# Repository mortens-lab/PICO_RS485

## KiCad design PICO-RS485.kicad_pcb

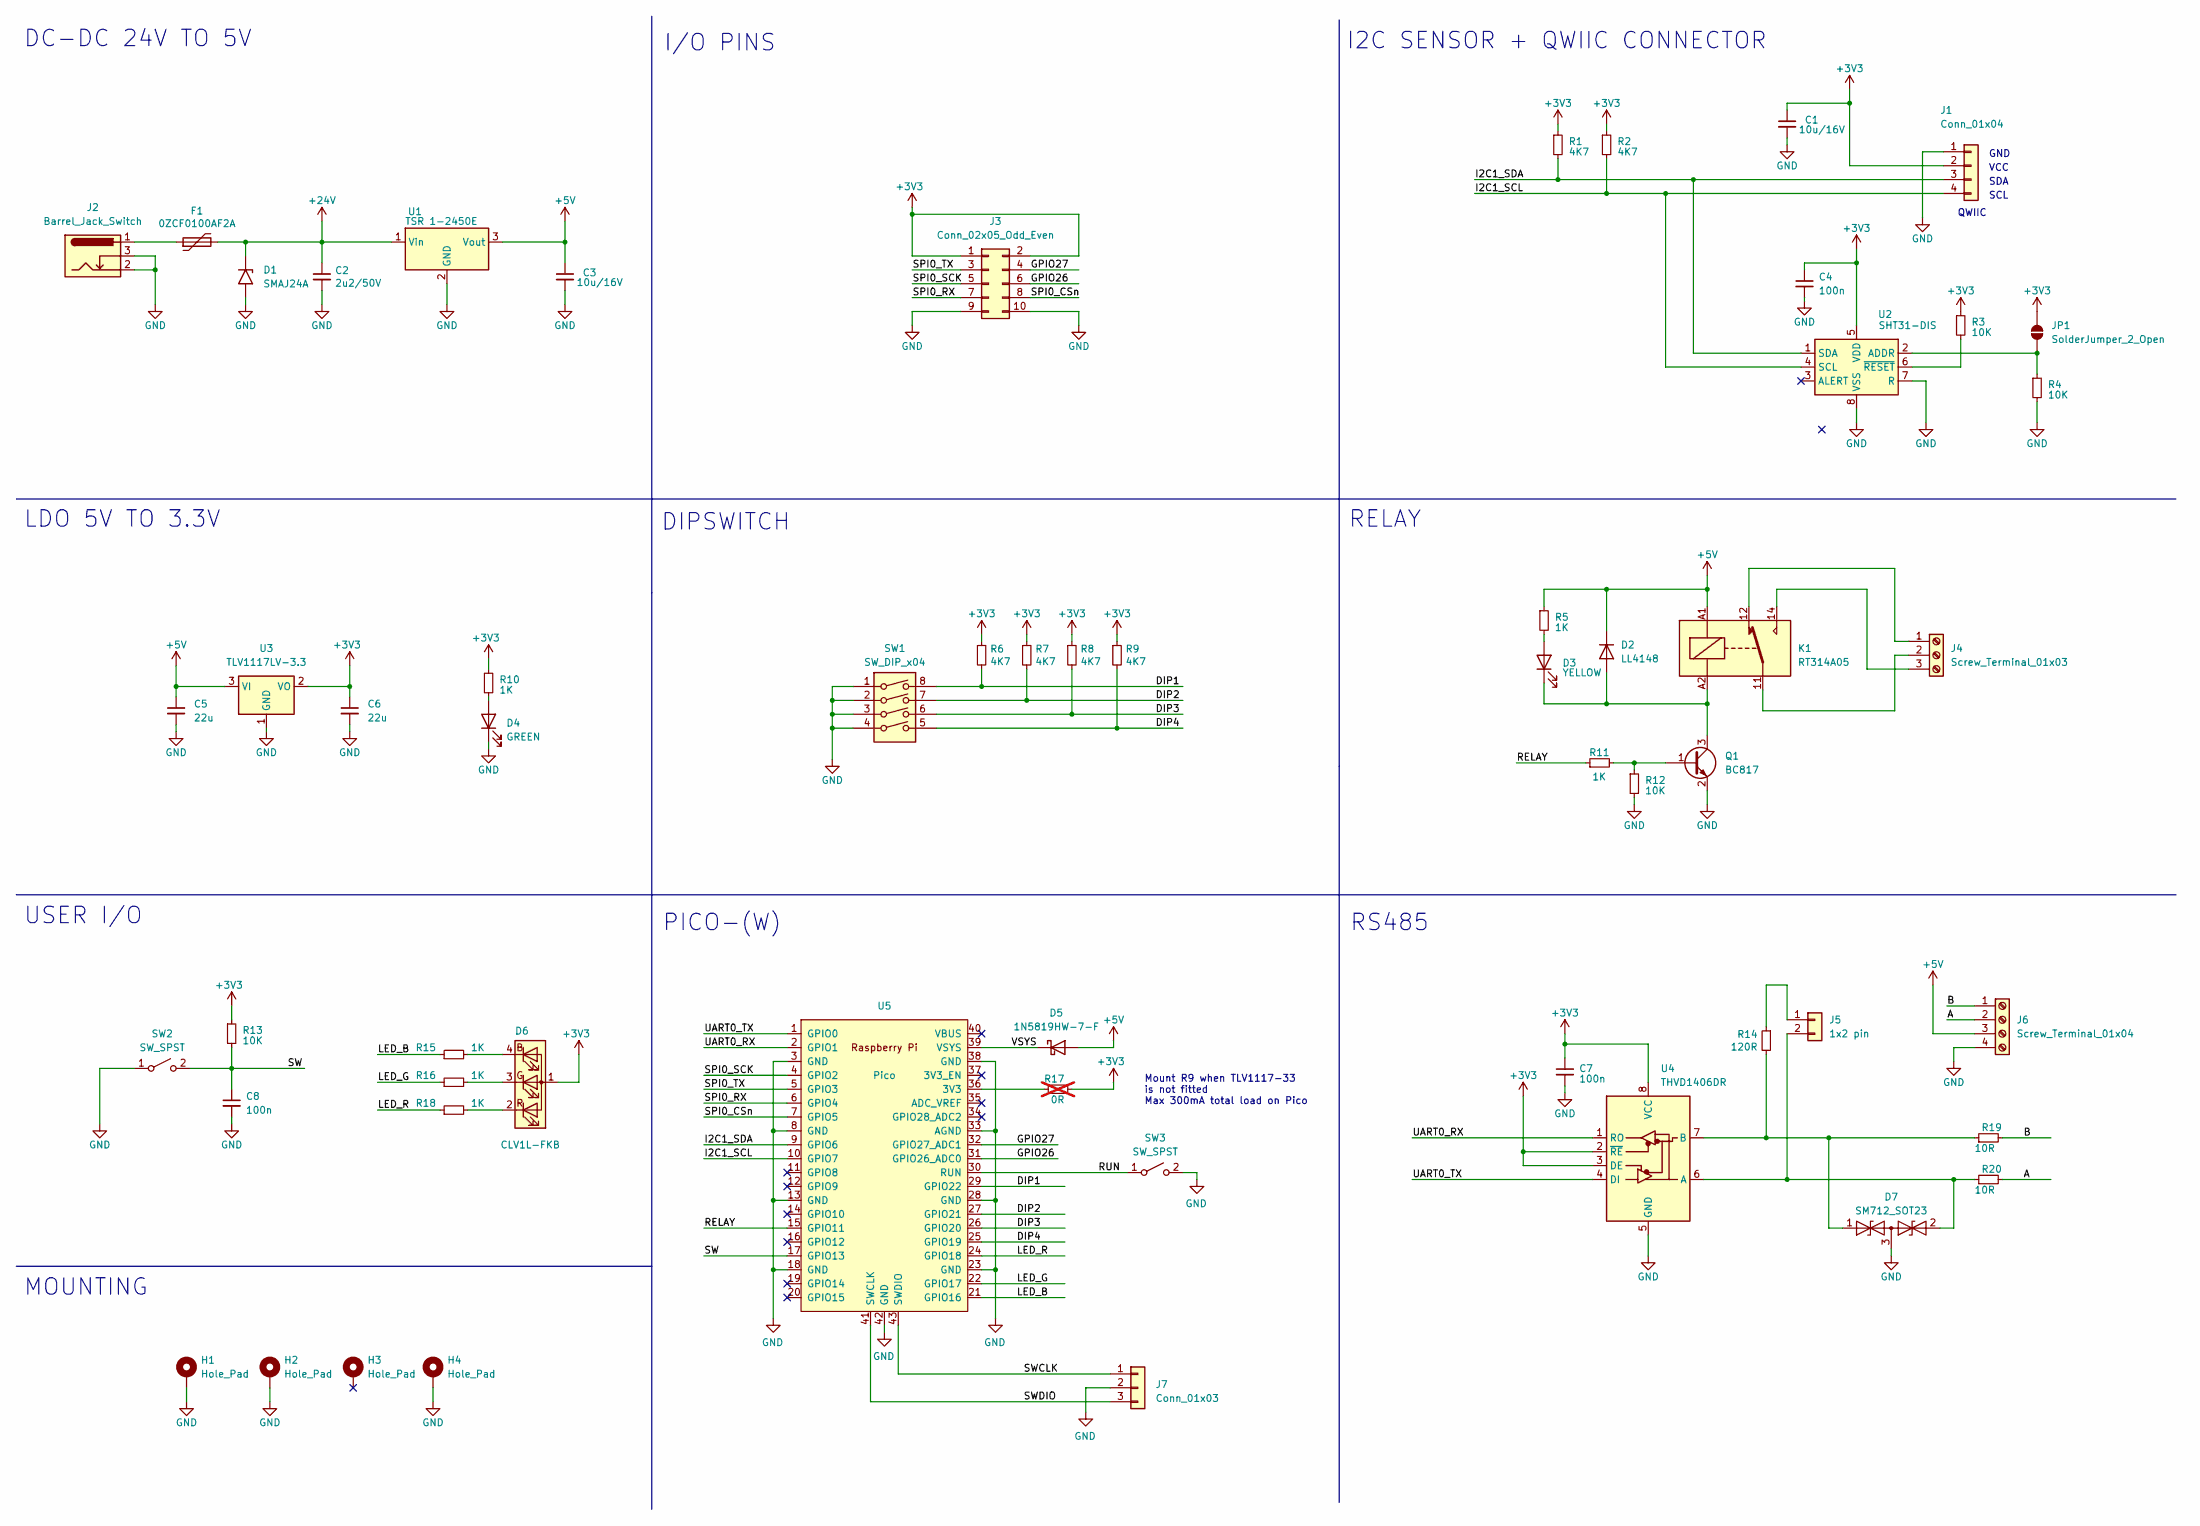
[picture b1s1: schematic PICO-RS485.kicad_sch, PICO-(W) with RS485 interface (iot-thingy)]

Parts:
C1, C3: 10u/16V; C_0805_2012Metric; Part Number CL21B106KOQNNNE; Mouser 187-CL21B106KOQNNNE
C2: 2u2/50V; C_0805_2012Metric; Part Number CL21B225KBYNNWE; Mouser 187-CL21B225KBYNNWE
C4, C7, C8: 100n; C_0402_1005Metric_Pad0.74x0.62mm_HandSolder; Manufacturer Part # GCM155R71H104KE02J; LCSC C2649549
C5, C6: 22u; C_0805_2012Metric_Pad1.18x1.45mm_HandSolder; Manufacturer Part # GRM21BR61A226ME51L; LCSC C77074
D1: SMAJ24A; D_SMA; Manufacturer Part # SMAJ24A; LCSC C148222
D2: LL4148; D_MiniMELF; Manufacturer Part # LL4148; LCSC C402260
D3: YELLOW; LED_0603_1608Metric_Pad1.05x0.95mm_HandSolder; Manufacturer Part # APTD1608LSYCK; LCSC C5352634
D4: GREEN; LED_0603_1608Metric_Pad1.05x0.95mm_HandSolder; Manufacturer Part # APHD1608LCGCK; LCSC C5139863
D5: 1N5819HW-7-F; D_SOD-323; Manufacturer Part # 1N5819HW-7-F; LCSC C82544
D6: CLV1L-FKB; LED_Cree-PLCC4_3.2x2.8mm_CCW; Manufacturer Part # CLV1L-FKB-CJ1N1E1BB7B3B3; LCSC NA
D7: SM712_SOT23; SOT-23; Manufacturer Part # SM712-02HTG; LCSC C172881
F1: 0ZCF0100AF2A; Fuse_2920_7451Metric; Part Number 0ZCF0100AF2A; Mouser 530-0ZCF0100AF2A
H1, H2, H4: Hole_Pad; MountingHole_3.2mm_M3_DIN965_Pad_TopBottom; Manufacturer Part # DNP; LCSC DNP
H3: Hole_Pad; MountingHole_3.2mm_M3_DIN965; Manufacturer Part # DNP; LCSC DNP
J1: Conn_01x04; JST_SH_SM04B-SRSS-TB_1x04-1MP_P1.00mm_Horizontal; Manufacturer Part # JST SM04B-SRSS-TB(LF)(SN); LCSC C160404
J2: Barrel_Jack_Switch; BarrelJack_Wuerth_6941xx301002; Manufacturer Part # 694106301002; LCSC C720557
J3: Conn_02x05_Odd_Even; PinHeader_2x05_P2.54mm_Vertical; Manufacturer Part # PZ2.54-2X5P-H25; LCSC C42431818
J4: Screw_Terminal_01x03; TerminalBlock_Phoenix_PT-1,5-3-5.0-H_1x03_P5.00mm_Horizontal; Manufacturer Part # 1984633; LCSC C5144867
J5: 1x2 pin; PinHeader_1x02_P2.54mm_Vertical; Part Number DNP; Mouser NA
J6: Screw_Terminal_01x04; TerminalBlock_Phoenix_PT-1,5-4-3.5-H_1x04_P3.50mm_Horizontal; Manufacturer Part # 1935174; LCSC C3816891
J7: Conn_01x03; PinHeader_1x03_P2.54mm_Vertical; Manufacturer Part # DNP; Mouser DNP
JP1: SolderJumper_2_Open; SolderJumper-2_P1.3mm_Open_RoundedPad1.0x1.5mm
K1: RT314A05; Relay_SPDT_Schrack-RT1-16A-FormC_RM5mm; Manufacturer Part # RT314005; LCSC C7065270
Q1: BC817; SOT-23; Manufacturer Part # BC817-40,235; LCSC C503453
R1, R2, R6, R7, R8, R9: 4K7; R_0402_1005Metric_Pad0.72x0.64mm_HandSolder; Manufacturer Part # CRCW04024K70FKED; Mouser 71-CRCW0402-4.7K-E3
R3, R4, R12, R13: 10K; R_0402_1005Metric_Pad0.72x0.64mm_HandSolder; Manufacturer Part # CRCW040210K0FKED; LCSC C71617
R5, R10, R11, R15, R16, R18: 1K; R_0402_1005Metric_Pad0.72x0.64mm_HandSolder; Manufacturer Part # CRCW04021K00FKED; LCSC C71623
R14: 120R; R_1206_3216Metric_Pad1.30x1.75mm_HandSolder; Manufacturer Part # CRCW1206120RFKEAC; Mouser 71-CRCW1206120RFKEAC
R17: 0R; R_0603_1608Metric; Manufacturer Part # RC0603JR-070RL; Mouser 603-RC0603JR-070RL; not fitted
R19, R20: 10R; R_0402_1005Metric_Pad0.72x0.64mm_HandSolder; Manufacturer Part # CRCW040210R0FKED; LCSC C481926
SW1: SW_DIP_x04; SW_DIP_SPSTx04_Slide_Omron_A6S-410x_W8.9mm_P2.54mm; Manufacturer Part # A6S-4101-H; LCSC C5123696
SW2: SW_SPST; SW_Tactile_SPST_Angled_PTS645Vx31-2LFS; Manufacturer Part # DTSA-61K-V; LCSC C483771
SW3: SW_SPST; SW_SPST_B3U-1000P
U1: TSR 1-2450E; Converter_DCDC_TRACO_TSR-1_THT; Part Number TSR 1-2450E; Mouser 495-TSR1-2450E
U2: SHT31-DIS; Sensirion_DFN-8-1EP_2.5x2.5mm_P0.5mm_EP1.1x1.7mm; Manufacturer Part # SHT31-DIS-F2.5kS; LCSC NA
U3: TLV1117LV-3.3; SOT-223-3_TabPin2; Manufacturer Part # TLV1117LV33DCYR; LCSC C48937499
U4: THVD1406DR; SOIC-8_3.9x4.9mm_P1.27mm; Manufacturer Part # HVD1406DR; LCSC C5215918
U5: Pico; Raspberry_Pi_Pico_SMT_THT; Manufacturer Part # Raspberry Pi PICO W; Mouser 358-SC0918

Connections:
+3V3: C1.1, C4.1, C6.1, C7.1, D6.1 (A), J1.2, J3.1, J3.2, JP1.2 (B), R1.1, R2.1, R3.1, R6.1, R7.1, R8.1, R9.1, R10.1, R13.1, R17.2, U2.5 (VDD), U3.2 (VO), U4.2 (~RE), U4.3 (DE), U4.8 (VCC)
+5V: C3.1, C5.1, D2.1 (K), D5.2 (A), J6.3, K1.A1, R5.1, U1.3 (Vout), U3.3 (VI)
+24V: C2.1, D1.1 (A1), F1.2, U1.1 (Vin)
/A: J6.2, R20.2
/B: J6.1, R19.2
/DIP1: R6.2, SW1.8, U5.29 (GPIO22)
/DIP2: R7.2, SW1.7, U5.27 (GPIO21)
/DIP3: R8.2, SW1.6, U5.26 (GPIO20)
/DIP4: R9.2, SW1.5, U5.25 (GPIO19)
/GPIO26: J3.6, U5.31 (GPIO26_ADC0)
/GPIO27: J3.4, U5.32 (GPIO27_ADC1)
/I2C1_SCL: J1.4, R2.2, U2.4 (SCL), U5.10 (GPIO7)
/I2C1_SDA: J1.3, R1.2, U2.1 (SDA), U5.9 (GPIO6)
/LED_B: R15.1, U5.21 (GPIO16)
/LED_G: R16.1, U5.22 (GPIO17)
/LED_R: R18.1, U5.24 (GPIO18)
/RELAY: R11.1, U5.15 (GPIO11)
/RUN: SW3.1 (A), U5.30 (RUN)
/SPI0_CSn: J3.8, U5.7 (GPIO5)
/SPI0_RX: J3.7, U5.6 (GPIO4)
/SPI0_SCK: J3.5, U5.4 (GPIO2)
/SPI0_TX: J3.3, U5.5 (GPIO3)
/SW: C8.1, R13.2, SW2.2 (B), U5.17 (GPIO13)
/SWCLK: J7.1, U5.43 (SWDIO)
/SWDIO: J7.3, U5.41 (SWCLK)
/UART0_RX: U4.1 (RO), U5.2 (GPIO1)
/UART0_TX: U4.4 (DI), U5.1 (GPIO0)
/VSYS: D5.1 (K), U5.39 (VSYS)
GND: C1.2, C2.2, C3.2, C4.2, C5.2, C6.2, C7.2, C8.2, D1.2 (A2), D4.1 (K), D7.3 (common), H1.1, H2.1, H4.1, J1.1, J2.2, J2.3, J3.9, J3.10, J6.4, J7.2, Q1.2 (E), R4.2, R12.2, SW1.1, SW1.2, SW1.3, SW1.4, SW2.1 (A), SW3.2 (B), U1.2 (GND), U2.7 (R), U2.8 (VSS), U2.9 (VSS), U3.1 (GND), U4.5 (GND), U5.3 (GND), U5.8 (GND), U5.13 (GND), U5.18 (GND), U5.23 (GND), U5.28 (GND), U5.33 (AGND), U5.38 (GND), U5.42 (GND)
unnamed: D2.2 (A), D3.1 (K), K1.A2, Q1.3 (C)
unnamed: D3.2 (A), R5.2
unnamed: D4.2 (A), R10.2
unnamed: D6.4 (BK), R15.2
unnamed: D6.3 (GK), R16.2
unnamed: D6.2 (RK), R18.2
unnamed: D7.1 (A1), R14.2, R19.1, U4.7 (B)
unnamed: D7.2 (A2), J5.2, R20.1, U4.6 (A)
unnamed: F1.1, J2.1
unnamed: J4.1, K1.12
unnamed: J4.2, K1.11
unnamed: J4.3, K1.14
unnamed: J5.1, R14.1
unnamed: JP1.1 (A), R4.1, U2.2 (ADDR)
unnamed: Q1.1 (B), R11.2, R12.1
unnamed: R3.2, U2.6 (~RESET)
unnamed: R17.1, U5.36 (3V3)

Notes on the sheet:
PICO-(W)
LDO 5V TO 3.3V
Mount R9 when TLV1117-33 is not fitted Max 300mA total load on Pico
USER I/O
RELAY
MOUNTING
SCL
I2C SENSOR + QWIIC CONNECTOR
SDA
I/O PINS
DIPSWITCH
QWIIC
VCC
RS485
GND
DC-DC 24V TO 5V

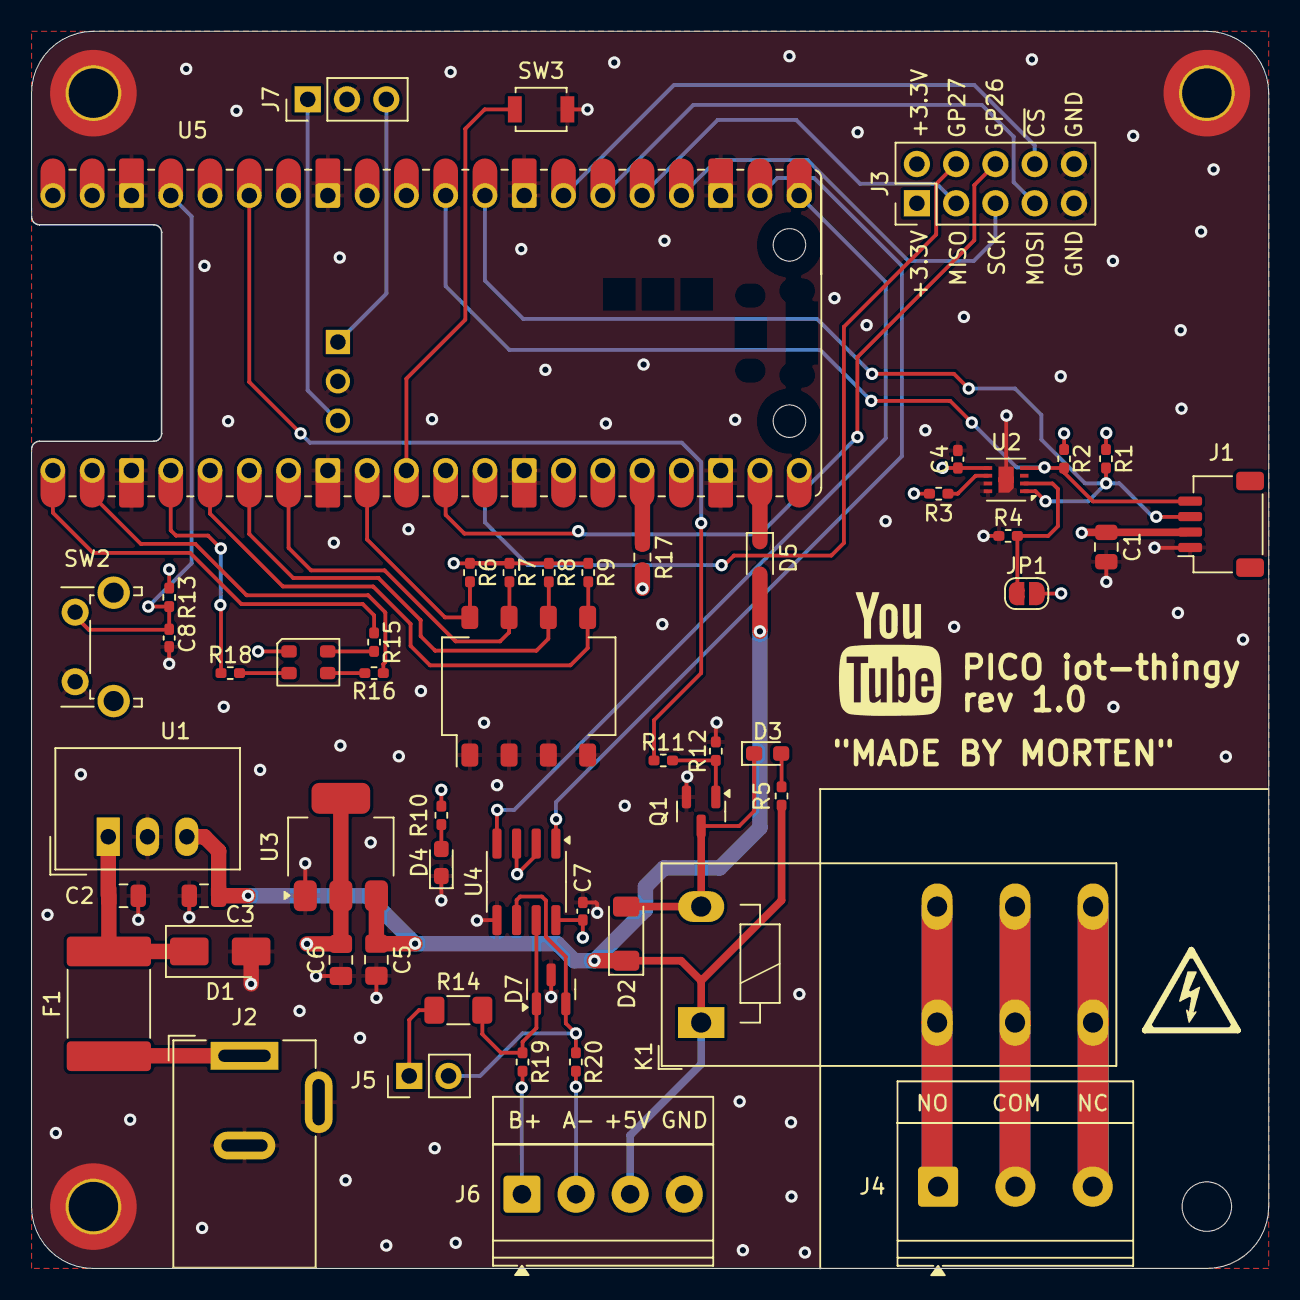
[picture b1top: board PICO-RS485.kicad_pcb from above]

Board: 4 copper layers, 80.0 x 79.9 mm, 58 parts (0 on the bottom side), 46 nets.
